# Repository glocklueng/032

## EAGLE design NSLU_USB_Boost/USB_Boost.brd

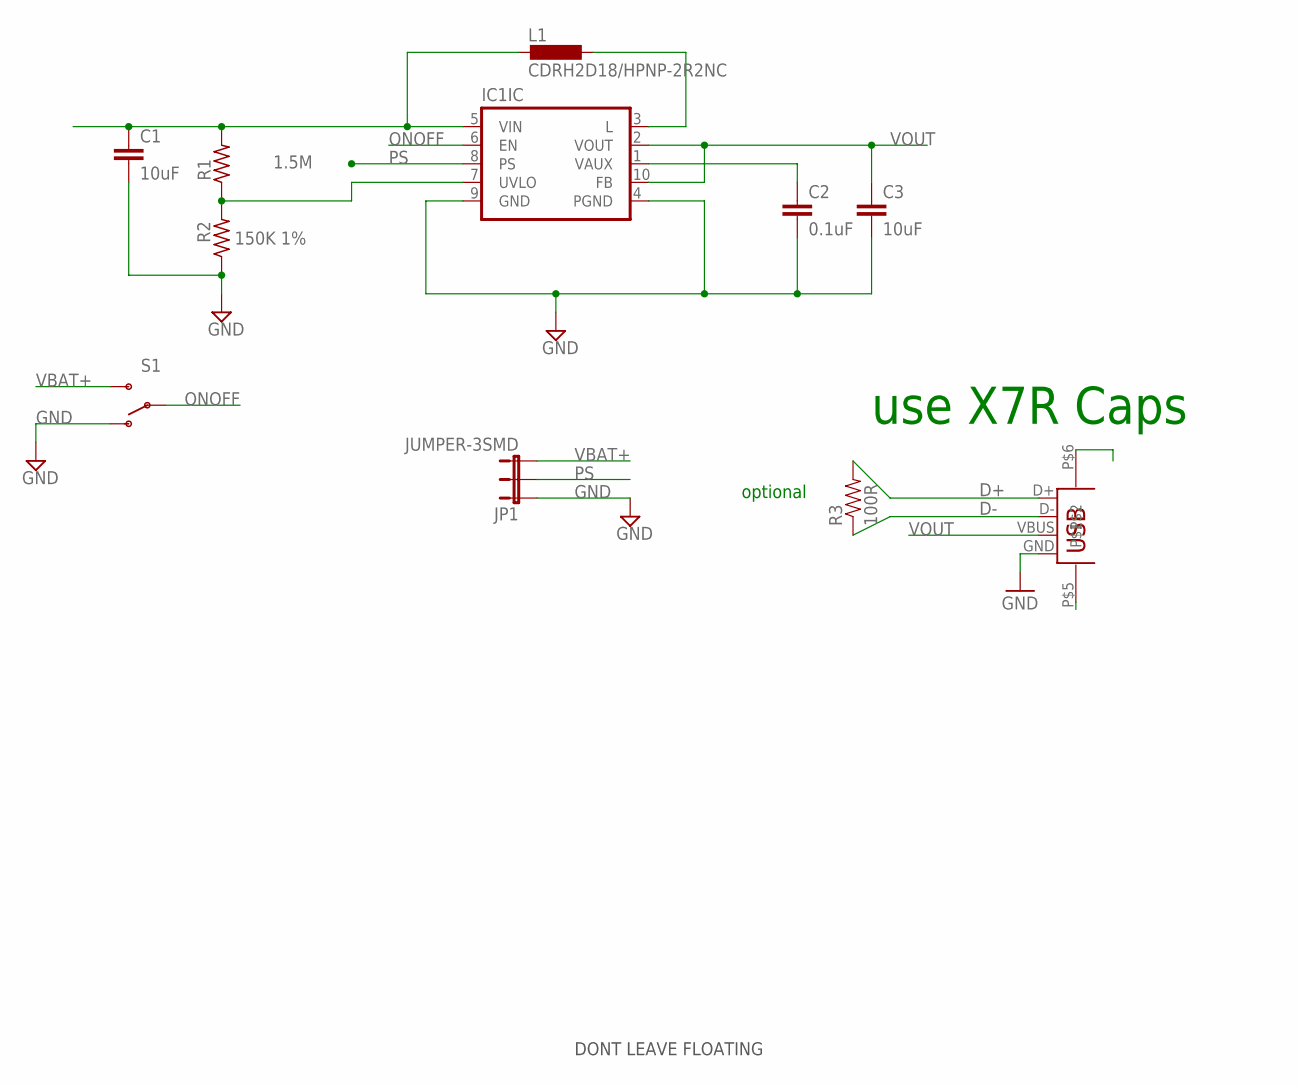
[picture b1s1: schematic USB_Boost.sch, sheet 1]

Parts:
C1, C3: 10uF; SPARKFUN_0603-CAP; PARTNO *
C2: 0.1uF; SPARKFUN_0603-CAP; MPN 02016D104KAT2A
IC1: IC_TPS6120XQFN10; QFN-10; PARTNO TPS61202DRCT
JP1: JUMPER-3SMD; SJ_3; PARTNO *
L1: CDRH2D18/HPNP-2R2NC; CDRH2D18; PARTNO *
R1: 1.5M; RLC_0603; TOLERANCE 5%; PARTNO *
R2: 150K 1%; RLC_0603; TOLERANCE 1%; PARTNO *
R3: 100R; 0805
S1: SWITCH-SPDT-SMD-A; SWITCH-SPST-SMD-A; PARTNO *
X1: USBKUSBX-SMT-AS1N; KSUBX-SMT-AS1N

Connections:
D+: R3.2, X1.D+
D-: R3.1, X1.D-
GND: C1.2, C2.2, C3.2, IC1.4 (PGND), IC1.9 (GND), IC1.P0 (GND), IC1.P1 (GND), IC1.P2 (GND), IC1.P3 (GND), IC1.P4 (GND), IC1.V0 (GND), IC1.V1 (GND), JP1.1, R2.1, S1.1 (O), X1.GND; also elsewhere on the board
GNDUSB: X1.P$5, X1.P$6
unnamed: C2.1, IC1.1 (VAUX)
unnamed: IC1.7 (UVLO), R1.1, R2.2
unnamed: IC1.3 (L), L1.P$2 (2)
ONOFF: IC1.6 (EN), S1.2
PS: IC1.8 (PS), JP1.2
VBAT+: C1.1, IC1.5 (VIN), JP1.3, L1.P$1 (1), R1.2, S1.3 (S)
VOUT: C3.1, IC1.2 (VOUT), IC1.10 (FB), X1.VBUS

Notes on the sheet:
use X7R Caps
optional
DONT LEAVE FLOATING

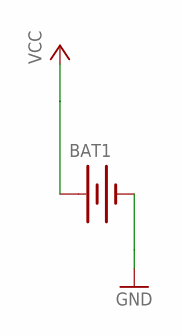
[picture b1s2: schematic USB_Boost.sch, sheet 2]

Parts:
BAT1: BATTERYCR123A; BATTERY_CR123A

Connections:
GND: BAT1.-; also elsewhere on the board
VCC: BAT1.+

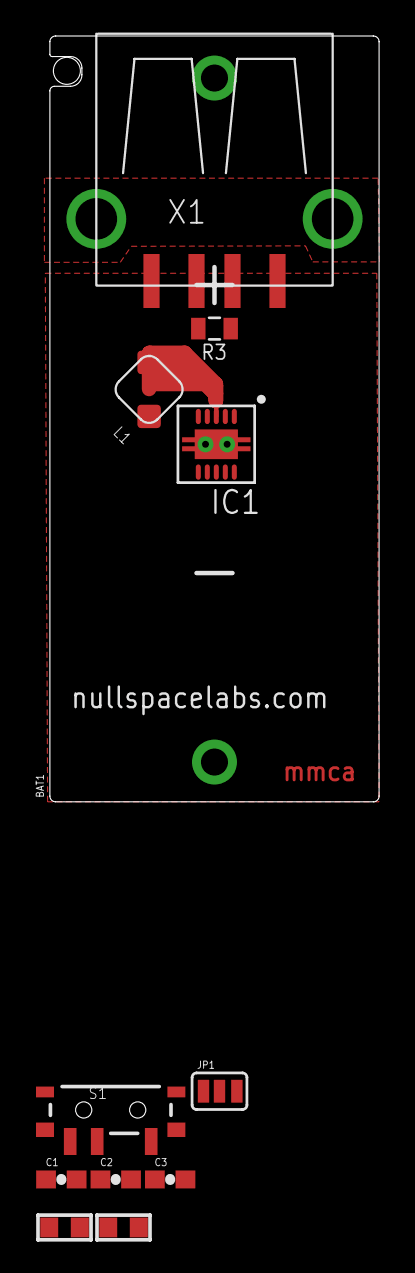
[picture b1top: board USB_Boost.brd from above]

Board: 2 copper layers, 18.3 x 42.5 mm, 12 parts (0 on the bottom side), 11 nets.

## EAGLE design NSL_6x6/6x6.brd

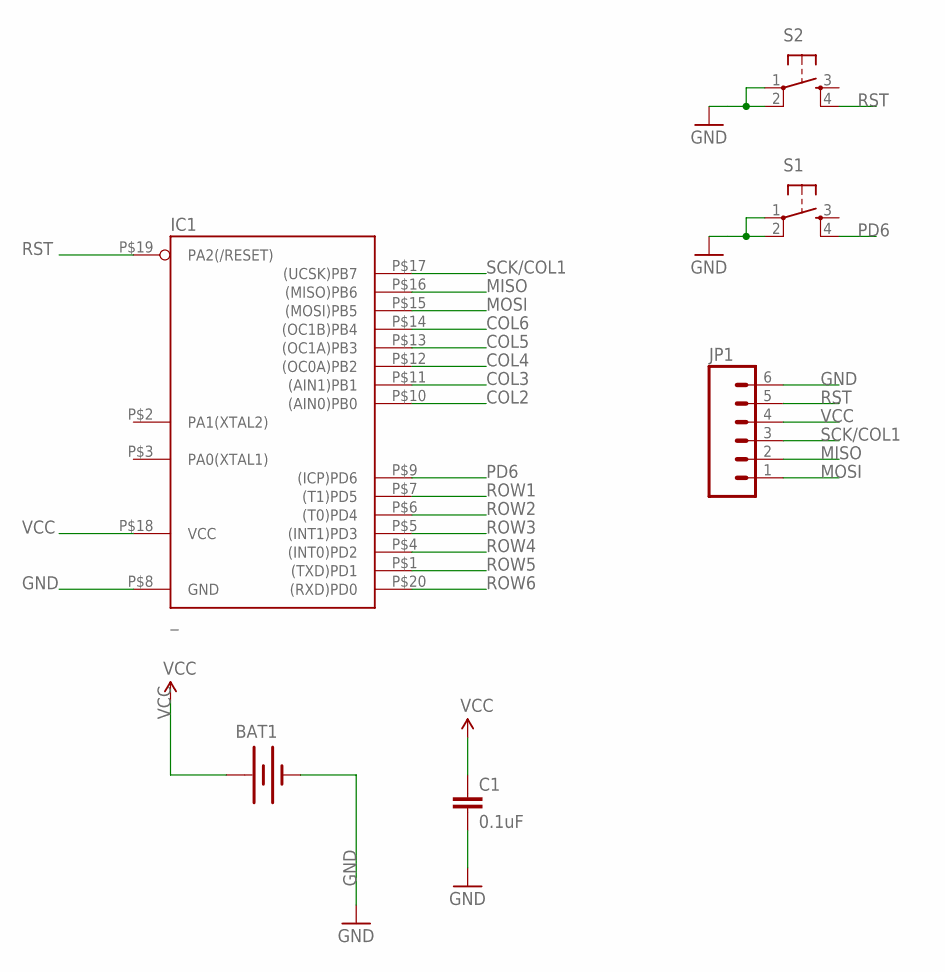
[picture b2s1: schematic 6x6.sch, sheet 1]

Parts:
BAT1: BATTERY245MM; BATTCON_245MM
C1: 0.1uF; 0805
IC1: _; MLF20
JP1: M061X06-SMD_EDGE_FEMALE; 1X06-SMD_EDGE
S1, S2: TAC_SWITCHSMD; TACTILE_SWITCH_SMD

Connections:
COL2: IC1.P$10 ((AIN0)PB0); also elsewhere on the board
COL3: IC1.P$11 ((AIN1)PB1); also elsewhere on the board
COL4: IC1.P$12 ((OC0A)PB2); also elsewhere on the board
COL5: IC1.P$13 ((OC1A)PB3); also elsewhere on the board
COL6: IC1.P$14 ((OC1B)PB4); also elsewhere on the board
GND: BAT1.2 (-), C1.2, IC1.P$8 (GND), JP1.6, S1.1, S1.2, S2.1, S2.2; also elsewhere on the board
MISO: IC1.P$16 ((MISO)PB6), JP1.2
MOSI: IC1.P$15 ((MOSI)PB5), JP1.1
PD6: IC1.P$9 ((ICP)PD6), S1.4
ROW1: IC1.P$7 ((T1)PD5); also elsewhere on the board
ROW2: IC1.P$6 ((T0)PD4); also elsewhere on the board
ROW3: IC1.P$5 ((INT1)PD3); also elsewhere on the board
ROW4: IC1.P$4 ((INT0)PD2); also elsewhere on the board
ROW5: IC1.P$1 ((TXD)PD1); also elsewhere on the board
ROW6: IC1.P$20 ((RXD)PD0); also elsewhere on the board
RST: IC1.P$19 (PA2(/RESET)), JP1.5, S2.4
SCK/COL1: IC1.P$17 ((UCSK)PB7), JP1.3; also elsewhere on the board
VCC: BAT1.3 (+), C1.1, IC1.P$18 (VCC), JP1.4; also elsewhere on the board

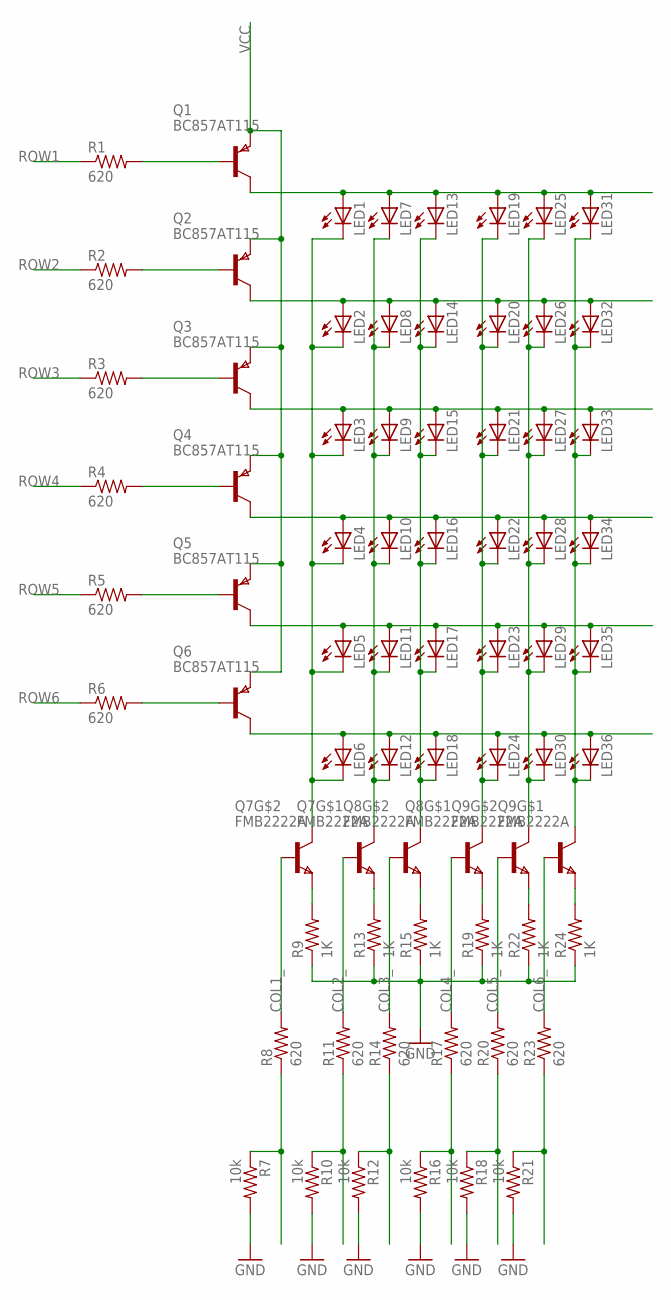
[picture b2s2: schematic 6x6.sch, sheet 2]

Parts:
LED1, LED2, LED3, LED4, LED5, LED6, LED7, LED8, LED9, LED10, LED11, LED12, LED13, LED14, LED15, LED16, LED17, LED18, LED19, LED20, LED21, LED22, LED23, LED24, LED25, LED26, LED27, LED28, LED29, LED30, LED31, LED32, LED33, LED34, LED35, LED36: LEDCHIPLED_1206; CHIPLED_1206
Q1, Q2, Q3, Q4, Q5, Q6: BC857AT115; SOT416
Q7, Q8, Q9: FMB2222A; SSOT6
R1: 620; SPARKFUN_0402-RES
R2, R3, R4, R5, R6, R8, R11, R14, R17, R20, R23: 620; SPARKFUN_0603-RES
R7, R10, R12, R16, R18, R21: 10k; SPARKFUN_0603-RES
R9, R13, R15, R19, R22, R24: 1K; SPARKFUN_0603-RES

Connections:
COL1_: Q7.3 (B), R8.2
COL2: R10.1, R11.1; also elsewhere on the board
COL2_: Q7.1 (B), R11.2
COL3: R12.1, R14.1; also elsewhere on the board
COL3_: Q8.3 (B), R14.2
COL4: R16.1, R17.1; also elsewhere on the board
COL4_: Q8.1 (B), R17.2
COL5: R18.1, R20.1; also elsewhere on the board
COL5_: Q9.3 (B), R20.2
COL6: R21.1, R23.1; also elsewhere on the board
COL6_: Q9.1 (B), R23.2
GND: R7.2, R9.1, R10.2, R12.2, R13.1, R15.1, R16.2, R18.2, R19.1, R21.2, R22.1, R24.1; also elsewhere on the board
LINE1: LED1.A, LED7.A, LED13.A, LED19.A, LED25.A, LED31.A, Q1.1 (C)
LINE2: LED2.A, LED8.A, LED14.A, LED20.A, LED26.A, LED32.A, Q2.1 (C)
LINE3: LED3.A, LED9.A, LED15.A, LED21.A, LED27.A, LED33.A, Q3.1 (C)
LINE4: LED4.A, LED10.A, LED16.A, LED22.A, LED28.A, LED34.A, Q4.1 (C)
LINE5: LED5.A, LED11.A, LED17.A, LED23.A, LED29.A, LED35.A, Q5.1 (C)
LINE6: LED6.A, LED12.A, LED18.A, LED24.A, LED30.A, LED36.A, Q6.1 (C)
unnamed: Q2.2 (B), R2.2
unnamed: Q1.2 (B), R1.2
unnamed: Q5.2 (B), R5.2
unnamed: Q3.2 (B), R3.2
unnamed: Q4.2 (B), R4.2
unnamed: Q6.2 (B), R6.2
unnamed: LED19.C, LED20.C, LED21.C, LED22.C, LED23.C, LED24.C, Q8.6 (C)
unnamed: LED25.C, LED26.C, LED27.C, LED28.C, LED29.C, LED30.C, Q9.4 (C)
unnamed: LED31.C, LED32.C, LED33.C, LED34.C, LED35.C, LED36.C, Q9.6 (C)
unnamed: Q7.2 (E), R9.2
unnamed: Q9.5 (E), R24.2
unnamed: Q9.2 (E), R22.2
unnamed: Q8.5 (E), R19.2
unnamed: Q8.2 (E), R15.2
unnamed: Q7.5 (E), R13.2
unnamed: LED1.C, LED2.C, LED3.C, LED4.C, LED5.C, LED6.C, Q7.4 (C)
unnamed: LED7.C, LED8.C, LED9.C, LED10.C, LED11.C, LED12.C, Q7.6 (C)
unnamed: LED13.C, LED14.C, LED15.C, LED16.C, LED17.C, LED18.C, Q8.4 (C)
ROW1: R1.1; also elsewhere on the board
ROW2: R2.1; also elsewhere on the board
ROW3: R3.1; also elsewhere on the board
ROW4: R4.1; also elsewhere on the board
ROW5: R5.1; also elsewhere on the board
ROW6: R6.1; also elsewhere on the board
SCK/COL1: R7.1, R8.1; also elsewhere on the board
VCC: Q1.3 (E), Q2.3 (E), Q3.3 (E), Q4.3 (E), Q5.3 (E), Q6.3 (E); also elsewhere on the board

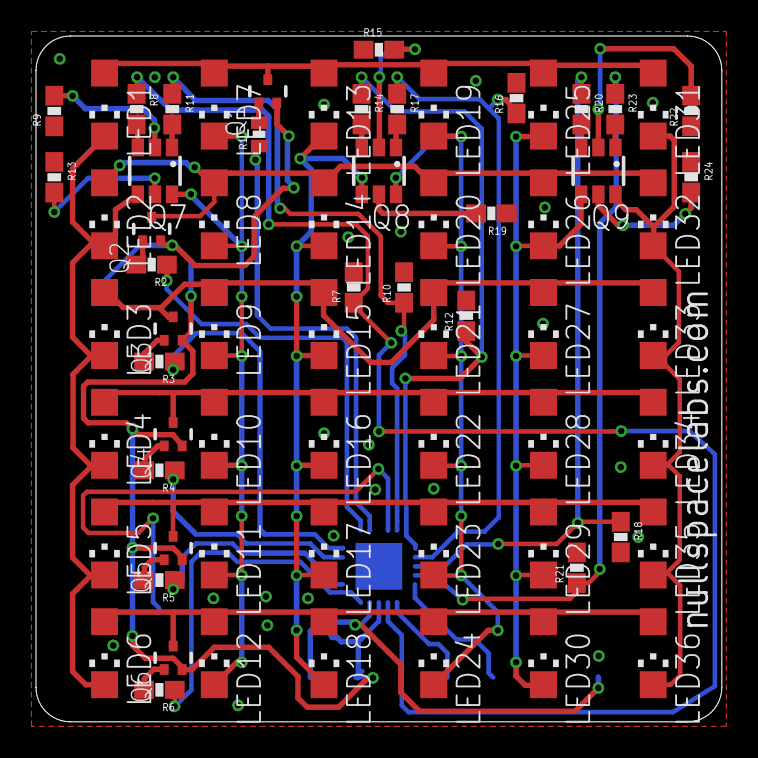
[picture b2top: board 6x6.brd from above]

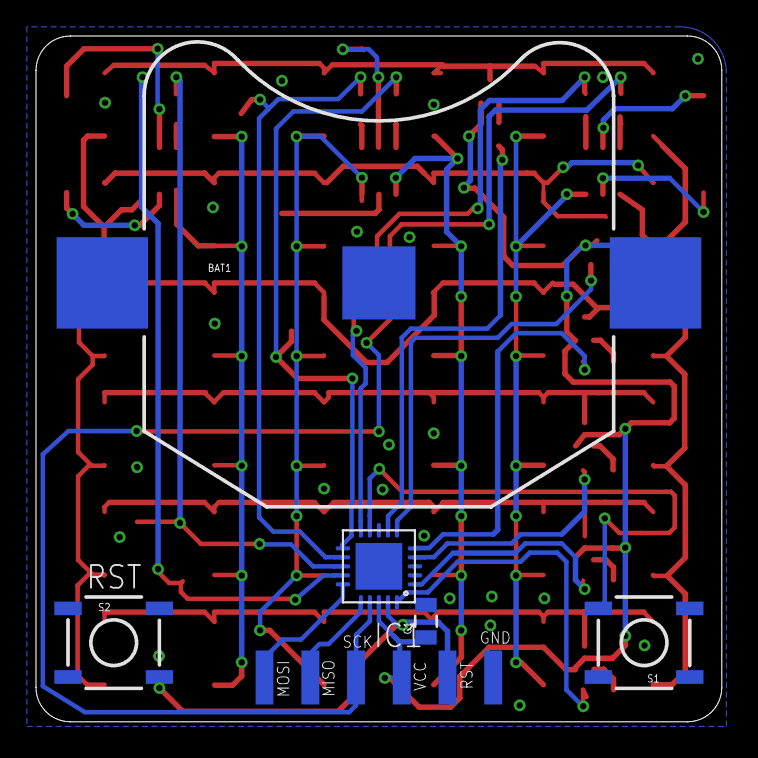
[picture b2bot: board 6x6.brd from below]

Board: 2 copper layers, 38.1 x 38.1 mm, 75 parts (6 on the bottom side), 48 nets.

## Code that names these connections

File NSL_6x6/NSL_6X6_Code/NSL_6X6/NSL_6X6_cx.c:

/*
 #     #                        #
 #     #                        #
 #     #                        #
 #######   ####    #####    #####   ####   #####    #####
 #     #  #    #  #    #   #    #  #    #  #    #  #
 #     #  ######  #    #   #    #  ######  #        ####
 #     #  #       #    #   #    #  #       #            #
 #     #   #####   ######   #####   #####  #       #####
*/

#include <avr/io.h> 
#include <avr/eeprom.h> 
#include <avr/interrupt.h>
#include <avr/pgmspace.h>
#include <util/delay.h>

#define shortdelay(); 			asm("nop\n\tnop\n\t");

#define TIMER1_PRESCALE_1 		(1)
#define TIMER1_PRESCALE_8 		(2)
#define TIMER1_PRESCALE_64 		(3)
#define TIMER1_PRESCALE_256		(4)
#define TIMER1_PRESCALE_1024	(5)

#define MIN_OF(x,y) ((x) < (y) ? (x) : (y))
#define MAX_OF(x,y) ((x) > (y) ? (x) : (y))

#define GET_BIT(a,n)    ((a >> n) & 1)
#define SET_BIT(a,n)    (a|=(1<<n))
#define CLR_BIT(a,n)    (a&=~(1<<n))
#define SWITCH_BIT(a,n) (a^=(1<<n))
#define IS_BIT_SET(a,n) (a & (1<<n))
#define IS_BIT_CLR(a,n) (~(a & (1<<n)))

// 		PORTB,DDRB,PIN
#define HEX__(n) 0x##n##LU

/* 8-bit conversion function */
#define B8__(x) ((x&0x0000000FLU)?1:0)	\
	+((x&0x000000F0LU)?2:0)		\
	+((x&0x00000F00LU)?4:0)		\
	+((x&0x0000F000LU)?8:0)		\
	+((x&0x000F0000LU)?16:0)	\
	+((x&0x00F00000LU)?32:0)	\
	+((x&0x0F000000LU)?64:0)	\
	+((x&0xF0000000LU)?128:0)

/* *** user macros ***/

/* for upto 8-bit binary constants */
#define B8(d) ((unsigned char)B8__(HEX__(d)))

/* for upto 16-bit binary constants, MSB first */
#define B16(dmsb,dlsb) (((unsigned short)B8(dmsb)<<	+ B8(dlsb)))

/* for upto 32-bit binary constants, MSB first */
#define B32(dmsb,db2,db3,dlsb) (((unsigned long)B8(dmsb)<<24)	 \
	+ ((unsigned long)B8(db2)<<16) \
	+ ((unsigned long)B8(db3)<<	 \
	+ B8(dlsb))




/*

Row:
1		2		3		4		5		6
PD5		PD4		PD3		PD2		PA0		PA1

Column:
1		2		3		4		5		6
PD6		PB0		PB1		PB2		PB3		PB4


*/

//  state definitions for each individual LED
// A5  A2  A1  A0  A4  A3
// PD6 PB0 PB1 PB2 PB3 PB4  

// 00 = LOW
// 01 = HIGH
// 11 = X (input)

#define D6_ON ( 1 << 0 )
#define DD_ON ( 1 << 1 )
#define BO_ON ( D6_ON | DD_ON )


static void SetLED( unsigned char row, unsigned char col ) 
{	
	PORTD &= ( _BV( PD0 ) | _BV( PD1 ) );
	PORTB &= ( _BV( PB5 ) | _BV( PB6 ) | _BV ( PB7) ) ;
	PORTA = 0;

	switch( col ) {
		case 0:
			PORTD   = _BV(PD6);
			break;
		case 1:
			PORTB  |= _BV(PB0);
			break;
		case 2:
			PORTB  |= _BV(PB1);
			break;
		case 3:
			PORTB  |= _BV(PB2);
			break;
		case 4:
			PORTB  |= _BV(PB3);
			break;
		case 5:
			PORTB  |= _BV(PB4);
			break;
	}
	
	// these are the rows
	PORTD |= _BV( PD5 ) | _BV( PD4 ) |_BV( PD3 ) | _BV( PD2 ) ;
	
	PORTA |= _BV( PA0 ) | _BV( PA1 );

}

unsigned int X = 0;


// This function delays the specified number of 10 microseconds
void delay_ten_us(unsigned long int us) 
{
	us /= 8;

  while (us != 0) {
	_delay_us(10);
    us--;
  }
}

int main(void)
{
	unsigned char R,C;
	unsigned int i;

	DDRA   = _BV( 0 ) | _BV( 1 );
	DDRB   =  (_BV(0) | _BV(1) |_BV(2) |_BV(3) |_BV(4) |_BV(5) );
	DDRD   = _BV( 6) |_BV( 5 ) | _BV( 4 ) |_BV( 3 ) |_BV( 2 );

	R = 0 ;
	C = 0 ;	
	i =0;	

	while( 1 ) 
	{
		PORTA=0;PORTD=0;PORTB=0;

		if( i > 10 ) 
			delay_ten_us(i	);

		if(C==5)
			i++;
	
		if( i== 900 ) 
			i=0;


		SetLED( R,C);
		R++ ; C++ ;
		if( R == 6 ) R = 0;
		if( C == 6 ) C = 0;

	}

}
